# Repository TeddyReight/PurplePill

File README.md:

# PurplePill

## Project Description

Minimal STM32 F4 Breakoutboard with USB-C and 10-pin SWD port.

STM32 NUCLEO boards do not have 10-pin SWD port and you are stuck with the provided ST-Link interface. I like using the BlackMagic GDB probe for development. https://github.com/blacksphere/blackmagic Checkout their amesome embeddded GDB server.

I think all projects should be using USB-C. I'm still running it in USB 2.0 mode. But the USB-C connector is the one to go with.
ST application note for moving legacy USB 2.0 to USB C (AN4775)
https://www.st.com/content/ccc/resource/technical/document/application_note/group0/a6/91/45/9e/12/a0/4d/42/DM00235987/files/DM00235987.pdf/jcr:content/translations/en.DM00235987.pdf

## 3D Image

<a href="https://oshpark.com/shared_projects/iZWzEnaZ"></img></a>

<br />This work is licensed under a <a rel="license" href="http://creativecommons.org/licenses/by-sa/4.0/">Creative Commons Attribution-ShareAlike 4.0 International License</a>.

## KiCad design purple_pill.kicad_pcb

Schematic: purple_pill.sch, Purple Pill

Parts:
C1, C2: 2.2uF; C_0805_2012Metric_Pad1.15x1.40mm_HandSolder
C3, C4: 20pF; C_0805_2012Metric_Pad1.15x1.40mm_HandSolder
C5, C6: 12.5pF; C_0805_2012Metric_Pad1.15x1.40mm_HandSolder
C7, C8, C9, C11: 100nF; C_0805_2012Metric_Pad1.15x1.40mm_HandSolder
J1, J2: Conn_01x24_MountingPin; PinHeader_1x24_P2.54mm_Vertical
J3: JTAG_SWD_10; PinHeader_2x05_P1.27mm_Vertical_SMD
J4: USB_C_Receptacle_USB2.0; USB_C_Receptacle_Amphenol_12401610E4-2A
JP1, JP2, JP4, JP6: Jumper_NC_Small; SolderJumper-2_P1.3mm_Open_TrianglePad1.0x1.5mm
JP3: Jumper_3_Bridged12; SolderJumper-3_P2.0mm_Open_TrianglePad1.0x1.5mm_NumberLabels
R1, R2, R6, R7: 22R; R_0805_2012Metric_Pad1.15x1.40mm_HandSolder
R3, R4, R5: 10K; R_0805_2012Metric_Pad1.15x1.40mm_HandSolder
R8, R9: 5R1K; R_0805_2012Metric_Pad1.15x1.40mm_HandSolder
U1: STM32F405RGTx; LQFP-64_10x10mm_P0.5mm
U2: LD1117S33TR_SOT223; SOT-223-3_TabPin2
X1: 8Mhz; Crystal_SMD_Abracon_ABM8G-4Pin_3.2x2.5mm
X2: 32.768KHz; Crystal_SMD_3215-2Pin_3.2x1.5mm

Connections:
+3V3: C7.1, C8.1, C9.1, J1.1, J2.1, J3.1, JP3.3, JP4.2, JP6.2, R3.2, R4.2, R5.2, U1.19 (VDD), U1.32 (VDD), U1.48 (VDD), U1.64 (VDD), U2.2
/PA0: J1.2, U1.14 (PA0)
/PA1: J1.3, U1.15 (PA1)
/PA2: J1.4, U1.16 (PA2)
/PA3: J1.5, U1.17 (PA3)
/PA4: J1.6, U1.20 (PA4)
/PA5: J1.7, U1.21 (PA5)
/PA6: J1.8, U1.22 (PA6)
/PA7: J1.9, U1.23 (PA7)
/PA8: J1.10, U1.41 (PA8)
/PA9: J1.11, U1.42 (PA9)
/PA10: J1.12, U1.43 (PA10)
/PA13: J1.13, U1.46 (PA13)
/PA14: J1.14, U1.49 (PA14)
/PA15: J1.15, U1.50 (PA15)
/PB0: J1.16, U1.26 (PB0)
/PB1: J1.17, U1.27 (PB1)
/PB2: J1.18, U1.28 (PB2)
/PB4: J1.19, U1.56 (PB4)
/PB5: J1.20, U1.57 (PB5)
/PB6: J1.21, U1.58 (PB6)
/PB7: J1.22, U1.59 (PB7)
/PB8: J2.17, U1.61 (PB8)
/PB9: J2.18, U1.62 (PB9)
/PB10: J2.19, U1.29 (PB10)
/PB11: J2.20, U1.30 (PB11)
/PB12: J2.21, U1.33 (PB12)
/PB15: J2.22, U1.36 (PB15)
/PC0: J2.2, U1.8 (PC0)
/PC1: J2.3, U1.9 (PC1)
/PC2: J2.4, U1.10 (PC2)
/PC3: J2.5, U1.11 (PC3)
/PC4: J2.6, U1.24 (PC4)
/PC5: J2.7, U1.25 (PC5)
/PC6: J2.8, U1.37 (PC6)
/PC7: J2.9, U1.38 (PC7)
/PC8: J2.10, U1.39 (PC8)
/PC9: J2.11, U1.40 (PC9)
/PC10: J2.12, U1.51 (PC10)
/PC11: J2.13, U1.52 (PC11)
/PC12: J2.14, U1.53 (PC12)
/PC13: J2.15, U1.2 (PC13)
/PD2: J2.16, U1.54 (PD2)
/RESET: J3.10, U1.7 (NRST)
GND: C1.2, C2.2, C3.2, C4.2, C5.2, C6.2, C7.2, C8.2, C9.2, C11.2, J1.23, J1.24, J2.23, J2.24, J3.3, J3.5, J3.9, J4.A1, J4.A12, J4.B1, J4.B12, J4.S1, JP1.1, JP2.1, JP3.2, R8.2, R9.2, U1.12 (VSSA), U1.18 (VSS), U1.63 (VSS), U2.1, X1.2, X1.4
unnamed: C1.1, JP1.2, U1.31 (VCAP_1)
unnamed: C2.1, JP2.2, U1.47 (VCAP_2)
unnamed: C3.1, U1.5 (PH0), X1.3
unnamed: C4.1, U1.6 (PH1), X1.1
unnamed: C5.1, U1.3 (PC14), X2.1
unnamed: C6.1, U1.4 (PC15), X2.2
unnamed: C11.1, J4.A4, J4.A9, J4.B4, J4.B9, U2.3
unnamed: J3.2, R2.2, R4.1
unnamed: J3.4, R3.1, U1.35 (PB14)
unnamed: J3.6, R1.2, R5.1
unnamed: J4.A5, R8.1
unnamed: J4.A6, J4.B6, R7.1
unnamed: J4.A7, J4.B7, R6.1
unnamed: J4.B5, R9.1
unnamed: JP3.1, U1.60 (BOOT0)
unnamed: JP4.1, U1.1 (VBAT)
unnamed: JP6.1, U1.13 (VDDA)
unnamed: R1.1, U1.55 (PB3)
unnamed: R2.1, U1.34 (PB13)
unnamed: R6.2, U1.44 (PA11)
unnamed: R7.2, U1.45 (PA12)

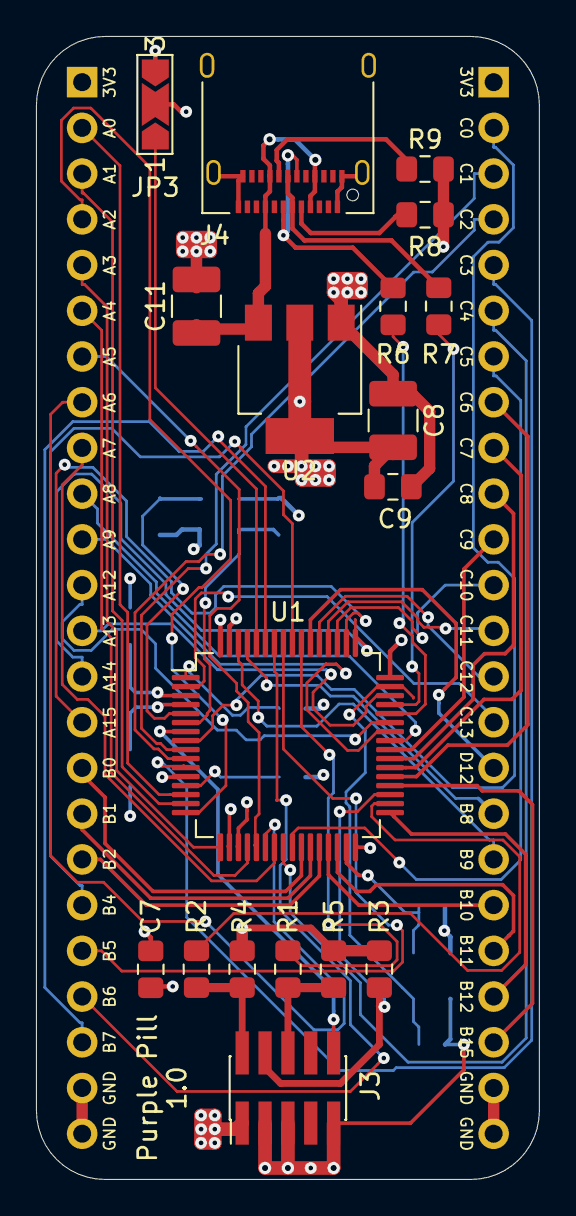
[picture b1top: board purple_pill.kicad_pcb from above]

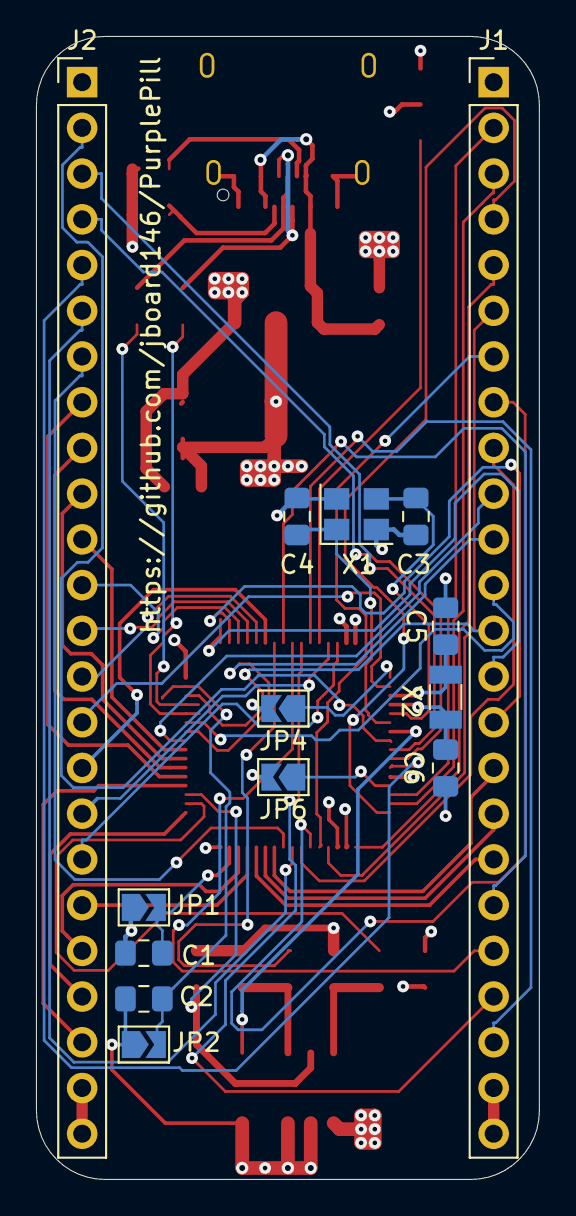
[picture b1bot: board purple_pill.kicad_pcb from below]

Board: 4 copper layers, 27.9 x 63.5 mm, 32 parts (14 on the bottom side), 66 nets.

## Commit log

2019-05-08 CC BY-SA 4.0
    CC BY-SA 4.0
2019-05-08 Initial Files
2019-05-09 Fixed my typo on pil vs pill... :(
    Committer: Jennifer Boardman <jboard@tux.boardman-engineering.net>
    On branch master
    Changes to be committed:
    new file: purple_pill.kicad_pcb
    new file: purple_pill.pro
    new file: purple_pill.sch
2019-05-11 Oscilators and Power
2019-05-12 Schmeatic Complete - Maybe...
2019-05-12 Initial Board Layout
2019-05-25 PCB Layout Complete
    On branch master
    Changes to be committed:
    modified: purple_pill.kicad_pcb
    modified: purple_pill.pro
    modified: purple_pill.sch
2019-05-25 Re-Ran AutoRoute
    On branch master
    Changes to be committed:
    modified: purple_pill.kicad_pcb
2019-05-25 Minor Edits
2019-05-25 More Minor Fixes...
2019-05-25 PDF Schematic, BOM (Still needs editing), 3D Image
    On branch master
    Changes to be committed:
    new file: 3d_PurplePill.png
    new file: purple_pill.csv
    new file: purple_pill.pdf
    modified: purple_pill.pro
2019-05-25 Minor Edits (Submitted to OSH Park)
2019-06-04 Update README.md
    added OSH Park Link
